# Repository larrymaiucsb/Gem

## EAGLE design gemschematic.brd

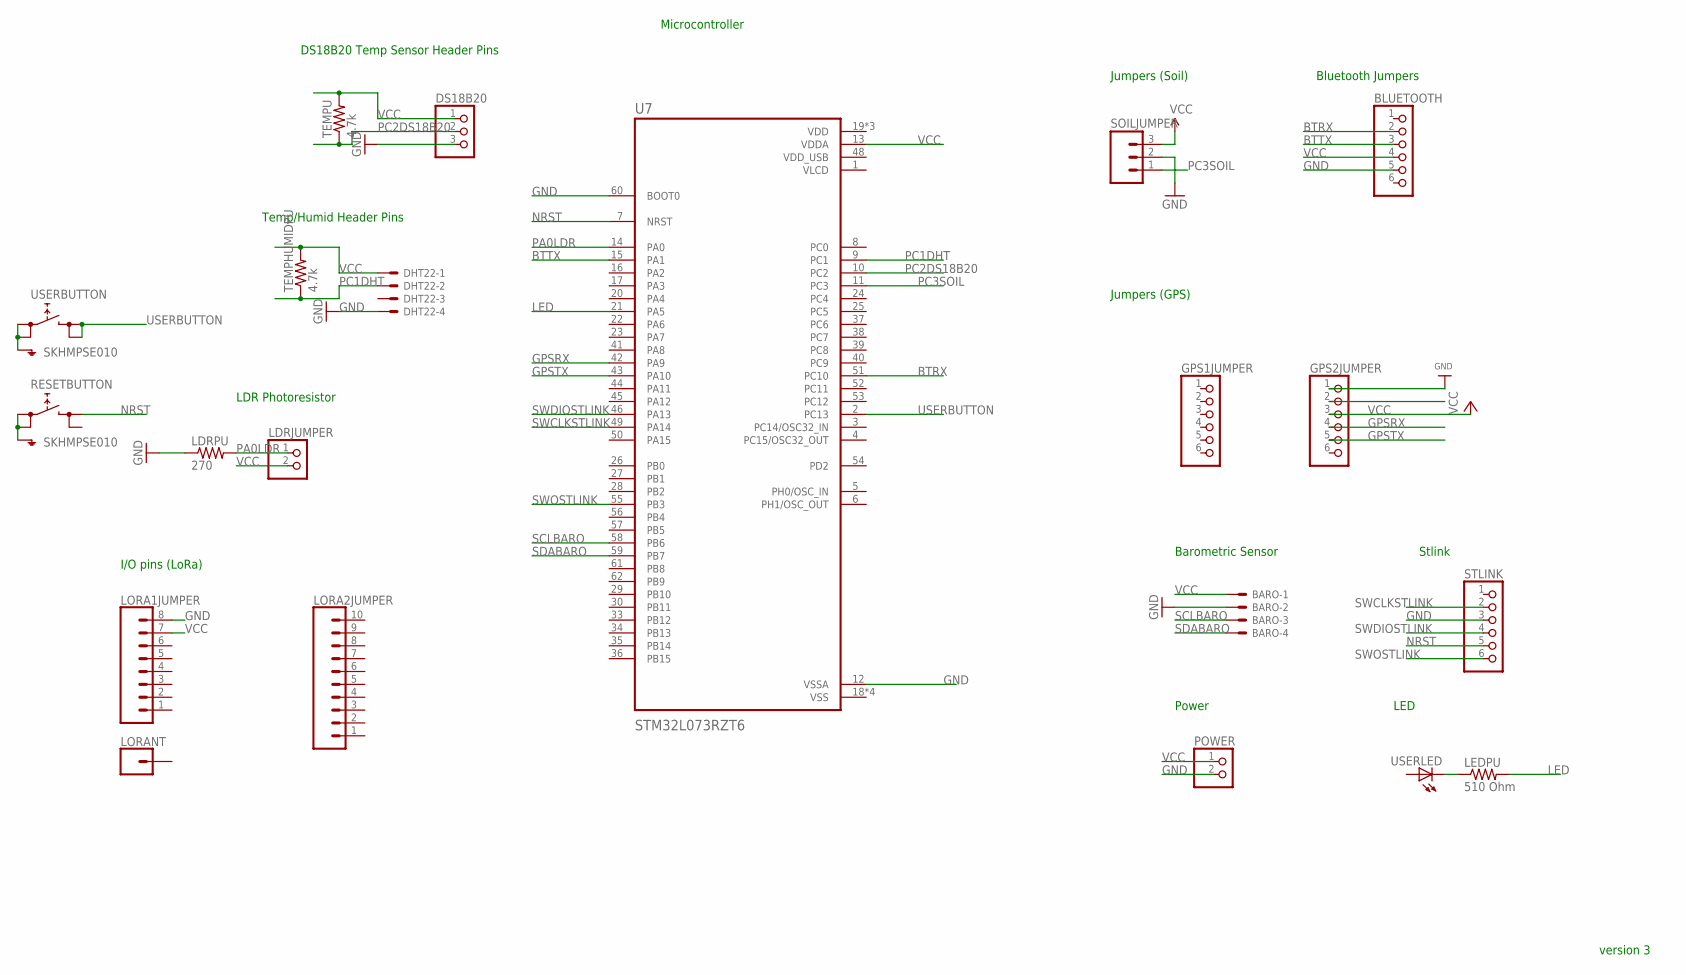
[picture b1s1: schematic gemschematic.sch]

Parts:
BARO: 22-23-2041
BLUETOOTH: PINHD-1X6; 1X06
DHT22: 22-23-2041
DS18B20: PINHD-1X3; 1X03
GPS1JUMPER, GPS2JUMPER: HEADER-1X670MIL; 1X06_ROUND_70
LDRJUMPER: PINHD-1X2; 1X02
LDRPU: 270; M0805
LEDPU: 510 Ohm; M0805
LORA1JUMPER: CONN_08NO_SILK_FEMALE_PTH; 1X08_NO_SILK
LORA2JUMPER: CONN_10NO_SILK_PTH_FEMALE; 1X10_NO_SILK
LORANT: CONN_01PTH_NO_SILK_YES_STOP; 1X01_NO_SILK
POWER: PINHD-1X2; 1X02
RESETBUTTON: SKHMPSE010; SKHMPXE010
SOILJUMPER: M03SCREW_LOCK; SCREWTERMINAL-3.5MM-3_LOCK.007S
STLINK: PINHD-1X6; 1X06
TEMPHUMIDPU: 4.7k; M0805
TEMPU: 4.7k; M0805
U7: STM32L073RZT6; QFP50P1200X1200X160-64N
USERBUTTON: SKHMPSE010; SKHMPXE010
USERLED: LED3MM

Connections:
1PPS: GPS2JUMPER.2
BTRX: BLUETOOTH.2, U7.51 (PC10)
BTTX: BLUETOOTH.3, U7.15 (PA1)
GND: BARO.2, BLUETOOTH.5, DHT22.4, DS18B20.3, GPS2JUMPER.1, LDRPU.1, LORA1JUMPER.8, POWER.2, SOILJUMPER.2, STLINK.3, U7.12 (VSSA), U7.60 (BOOT0)
GPSRX: GPS2JUMPER.4, U7.42 (PA9)
GPSTX: GPS2JUMPER.5, U7.43 (PA10)
LED: LEDPU.2, U7.21 (PA5)
unnamed: LEDPU.1, USERLED.K (C)
unnamed: USERBUTTON.1 (1.1), USERBUTTON.2 (1.2), USERBUTTON.5 (SH)
unnamed: RESETBUTTON.1 (1.1), RESETBUTTON.2 (1.2), RESETBUTTON.5 (SH)
NRST: RESETBUTTON.3 (2.1), STLINK.5, U7.7 (NRST)
PA0LDR: LDRJUMPER.1, LDRPU.2, U7.14 (PA0)
PC1DHT: DHT22.2, TEMPHUMIDPU.1, U7.9 (PC1)
PC2DS18B20: DS18B20.2, TEMPU.1, U7.10 (PC2)
PC3SOIL: SOILJUMPER.1, U7.11 (PC3)
SCLBARO: BARO.3, U7.58 (PB6)
SDABARO: BARO.4, U7.59 (PB7)
SWCLKSTLINK: STLINK.2, U7.49 (PA14)
SWDIOSTLINK: STLINK.4, U7.46 (PA13)
SWOSTLINK: STLINK.6, U7.55 (PB3)
USERBUTTON: U7.2 (PC13), USERBUTTON.3 (2.1), USERBUTTON.4 (2.2)
VCC: BARO.1, BLUETOOTH.4, DHT22.1, DS18B20.1, GPS2JUMPER.3, LDRJUMPER.2, LORA1JUMPER.7, POWER.1, SOILJUMPER.3, TEMPHUMIDPU.2, TEMPU.2, U7.13 (VDDA)
VDD: U7.19 (VDD), U7.32 (VDD), U7.64 (VDD)
VDD_USB: U7.48 (VDD_USB)
VLCD: U7.1 (VLCD)
VSS: U7.18 (VSS), U7.31 (VSS), U7.47 (VSS), U7.63 (VSS)

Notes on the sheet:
Jumpers (Soil)
Temp/Humid Header Pins
Microcontroller
Jumpers (GPS)
I/O pins (LoRa)
DS18B20 Temp Sensor Header Pins
Barometric Sensor
LDR Photoresistor
Bluetooth Jumpers
version 3
Stlink
Power
LED

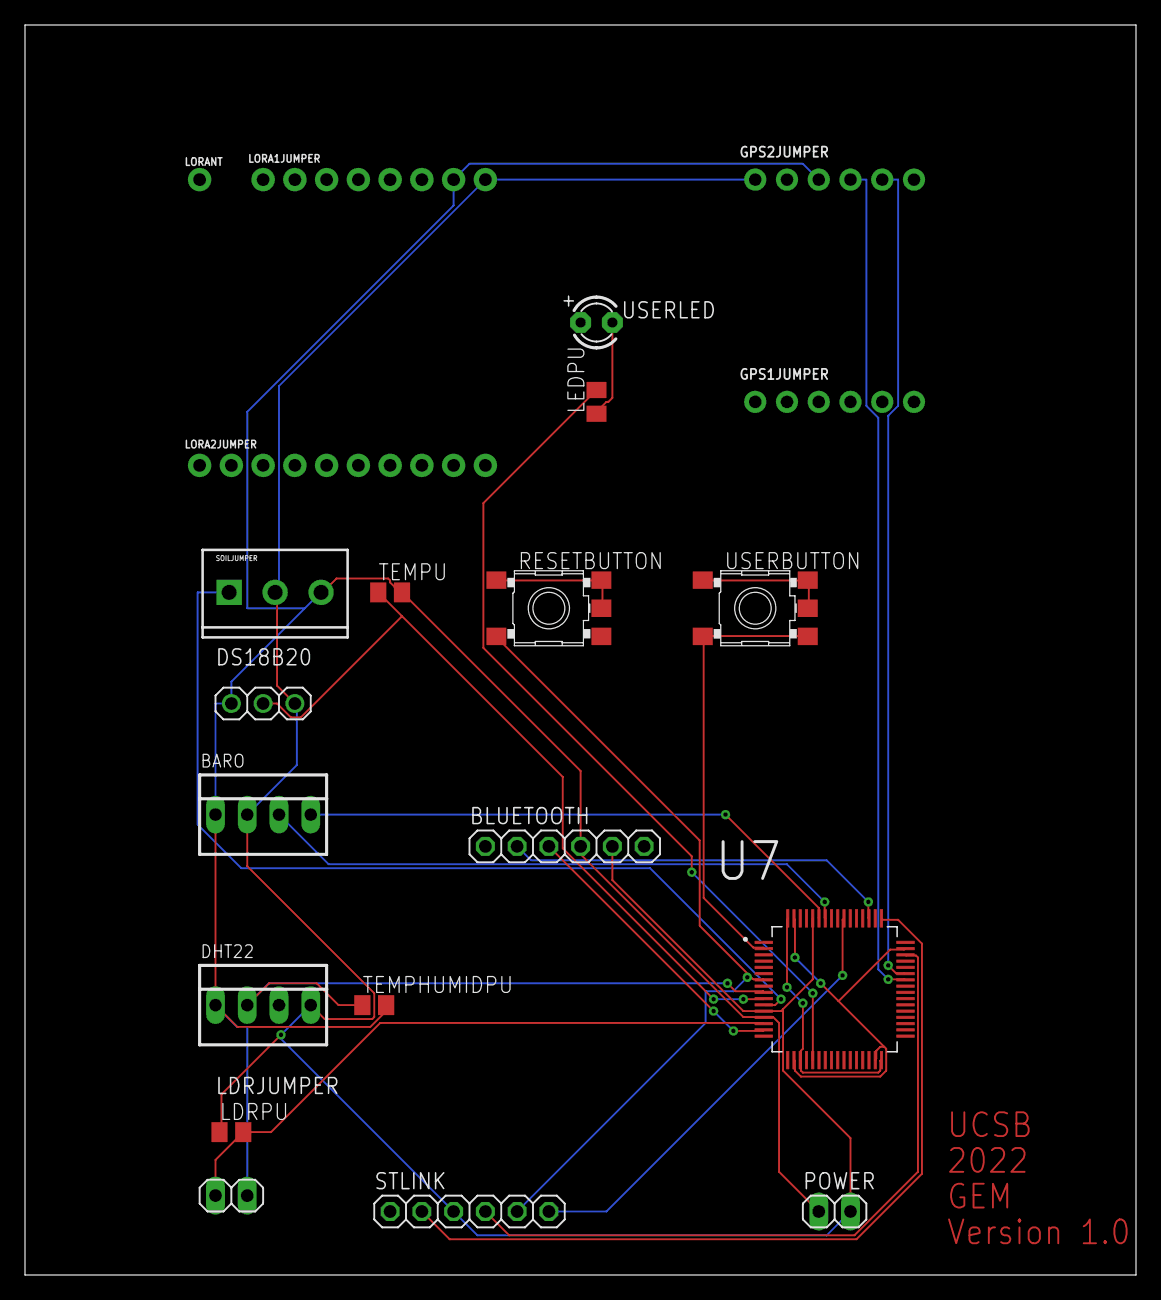
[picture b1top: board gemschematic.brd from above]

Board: 2 copper layers, 88.9 x 100.0 mm, 21 parts (0 on the bottom side), 23 nets.

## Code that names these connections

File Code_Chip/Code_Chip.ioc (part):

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Mcu.Name=STM32L072R(B-Z)Tx
Mcu.Package=LQFP64
Mcu.UserName=STM32L072RBTx
PA0.Mode=IN0
PA0.Signal=ADC_IN0
PA10.Mode=Asynchronous
PA10.Signal=USART1_RX
PA5.Signal=GPIO_Output
PA9.Mode=Asynchronous
PA9.Signal=USART1_TX
PB6.Mode=I2C
PB6.Signal=I2C1_SCL
PB7.Mode=I2C
PB7.Signal=I2C1_SDA
PC1.Signal=GPIO_Output
PC10.Signal=USART4_TX
PC11.Signal=USART4_RX
PC12.Mode=Asynchronous
PC12.Signal=USART5_TX
PC2.Signal=GPIO_Output
PC3.Mode=IN13
PC3.Signal=ADC_IN13
PD2.Mode=Asynchronous
PD2.Signal=USART5_RX
RCC.HSE_VALUE=8000000
RCC.SYSCLKFreq_VALUE=32000000
RCC.SYSCLKSource=RCC_SYSCLKSOURCE_PLLCLK
board=custom

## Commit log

2021-12-04 Create Humidity
2021-12-04 Create Soil
2021-12-04 Create Lora
2021-12-04 Create GPS
2021-12-07 GPS_UART
    Completed GPS Code, currently the Longitude & Latitude are held by a char pointer which will be helpful when communicating over LoRa.
2021-12-07 Update GPS
2021-12-07 GPS Sensor
    GPS Sensor is currently fully operational. The code is set up to have the Longitude and Latitude values sent over UART from GPS sensor to the STM32L496 microcontroller. The STMs receives the data in 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
2022-01-05 Update Humidity
2022-01-12 Create Temperature
2022-01-12 Create Everything
2022-01-20 Update and rename main.c to Alex's Mosh
2022-01-20 Schematic
    Added finished schematic
2022-01-27 Update Alex's Mosh
    SENSORS: GPS & SOIL MOISTURE
2022-02-10 PCB 2/10/22
2022-02-11 Rename LoRaNow_Node.ino to ESP32_Node.ino
2022-02-11 Rename ESP32_Node.ino to ESP32_NODE.ino
2022-02-17 Create main
2022-02-18 Create LoRaGatewayNoWifi.ino
    This is to configure a gateway without a Wi-Fi network, it will display serial data over COM port.
2022-02-18 Update and rename ESP32_NODE.ino to LoRaNode.ino
    This is to configure an ESP32 LoRa module to receive data over Bluetooth then sends it over LoRa on the 904.1 MHz frequency spectrum where a gateway will eventually receive it.
2022-03-11 Create HC05_ATCOMMAND.ino
    Code to pair the HC05 with an ESP32 over BT. Uses SoftwareSerial library.
2022-03-11 Rename HC05_ATCOMMAND.ino to HC05_AT_COMMAND_MODE.ino
2022-03-11 Newest Push - 3/11/2022
    Code to make the HC05 into AT Command Mode. Make sure to pull EN to 5V & press the physical button on the HC05 when powering on. Uses SoftwareSerial library for UART connectivity.
2022-03-11 LoRa_Node_HC05.ino
    This configuration is for an ESP32 set as a LoRaWAN transmitter (node) and will send messages received over Bluetooth on the LoRaWAN 904 MHz frequency spectrum.
2022-03-14 Add files via upload
    added butons
2022-03-18 added smd parts
2022-04-07 Testing...
2022-04-08 PCB now synced through this folder
2022-04-08 test_added text box on schematic
2022-04-08 tes2_replaced chip symbol
    same chip but w/ 3d model now
2022-04-08 headers chosen, not placed yet
2022-04-09 Altium migration complete, all components now w/ footprints & models
2022-04-09 moved old eagle files into separate folder
2022-04-09 Altium import from Eagle, components replace w/ equivalent
2022-04-09 completed rough component placement -> further optimization possible
2022-04-11 4/10/2022
2022-04-11 board cut, now rectangular, clearances ALL WRONG
2022-04-11 Add files via upload
    added adc code but need to config channel selection
2022-04-11 rectangle, need to check clearance and collision, add power, add sensor clip
2022-04-12 some placement changes, check clearance
2022-04-13 changed placement
2022-04-13 V2_0 & V2_1 -> _0 has BT sticking out
2022-04-14 ADDED BT correct pins
2022-04-14 fixed bluetooth pins some more
2022-04-14 gps spacing fixed to 0.8
2022-04-14 added a CubeIDE folder, added sensor test code
2022-04-14 added markers
2022-04-14 Add files via upload
    Everything tested and fully working (apart from Bluetooth, last sensor to be tested).
2022-04-18 4/17
    - added some dimensions
    - adding volt. conversion (not complete)
    - added some dimensions
2022-04-18 completed power supply design(9V-5V-3.3V)
    - power supply needs review
    - all components present for final PCB design
    - more dimensions need to be checked
    - clip for DS18B20 could be too small
2022-04-21 fixing lora
2022-04-21 routing almost done
    -check header orientations
    -check connections bt, lora and others(noted in schematic)
    -check BT voltage
2022-04-22 added power led
    some works to be done noted in schematic
2022-04-22 added usart lora
2022-04-27 routing completed
    -need to add pin names
    -need to remove markings
2022-04-27 routing completed
    -placed a logo as a trial
2022-04-28 added logo
2022-04-28 LABELS
2022-04-29 added production version
    -removed all dimension markers
2022-05-04 added a cleaned-up V2.2 version, plz work on this one
2022-05-11 Create LoRaNode_UART.ino
    Removes need for HC05.
2022-05-12 added matlab
2022-05-12 live plots of sensor readings, draft code
2022-05-14 5/14/22 code
2022-05-20 5/19/2022
2022-05-22 draft Matlab code, modified STM code
2022-05-26 cleaned up main(), get f() written down below
2022-05-26 changed folder name + code cleanup
2022-05-26 renamed folder, cleaned up main.c
2022-05-31 MATLAB code now displays all 3 nodes, cleaned up STM code
2022-06-01 fixed MATLAB code, added "ID" to STM code
2022-06-06 3d casing CAD files
2022-06-16 gateway and node code update

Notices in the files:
parts and their libraries:
SparkFun-Connectors: Licensing: Creative Commons ShareAlike 4.0 International - https://creativecommons.org/licenses/by-sa/4.0
microbuilder: This work is placed in the public domain, and may be freely used for commercial and non-commercial work with the following conditions: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
